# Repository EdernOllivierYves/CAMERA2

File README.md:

# CAMERA2
It is an upgrade with the DR specification of the optical sensor I have received 10th of june 2025.

I have designed the camera around the piece of metal "cache4", with the software autodesk FUSION, in order to complete my project.

Then it should be manufactured with the mechanical drawing, and the pieces of metal can be made at the website "www.usineur.fr".

BR, EO.

PS :  To solder the components you also need to buy capacitors and resistors, for example on the "www.mchobby.be" website.

Here again, I do join the list of the electronical components for soldering on the printed circuit board :

9 Capacitors of 10nF 50V

9 Capacitors of 100nF 50V

9 Capacitors of 10µF AVX 16V

7 Capacitors of 1µF AVX 25V

2 Capacitors electrolytic of 10µF 25V

19 x 36 Pin Header Female (for the socket of the optical sensor)

1 x 40 Pin Header Male (for the arduino connector of the FPGA board)

2 x 25 Pin Header Male (for the parallel port of the circuit board)

7 Potentiometers of 1KOhms 3296W

1 Sensor MT9M413STMDR

1 DEL 3mm

1 Resistor 430Ohms

1 Resistor 2K2Ohms

1 Resistor 10KOhms

1 Transistor BC550B TO92 45V

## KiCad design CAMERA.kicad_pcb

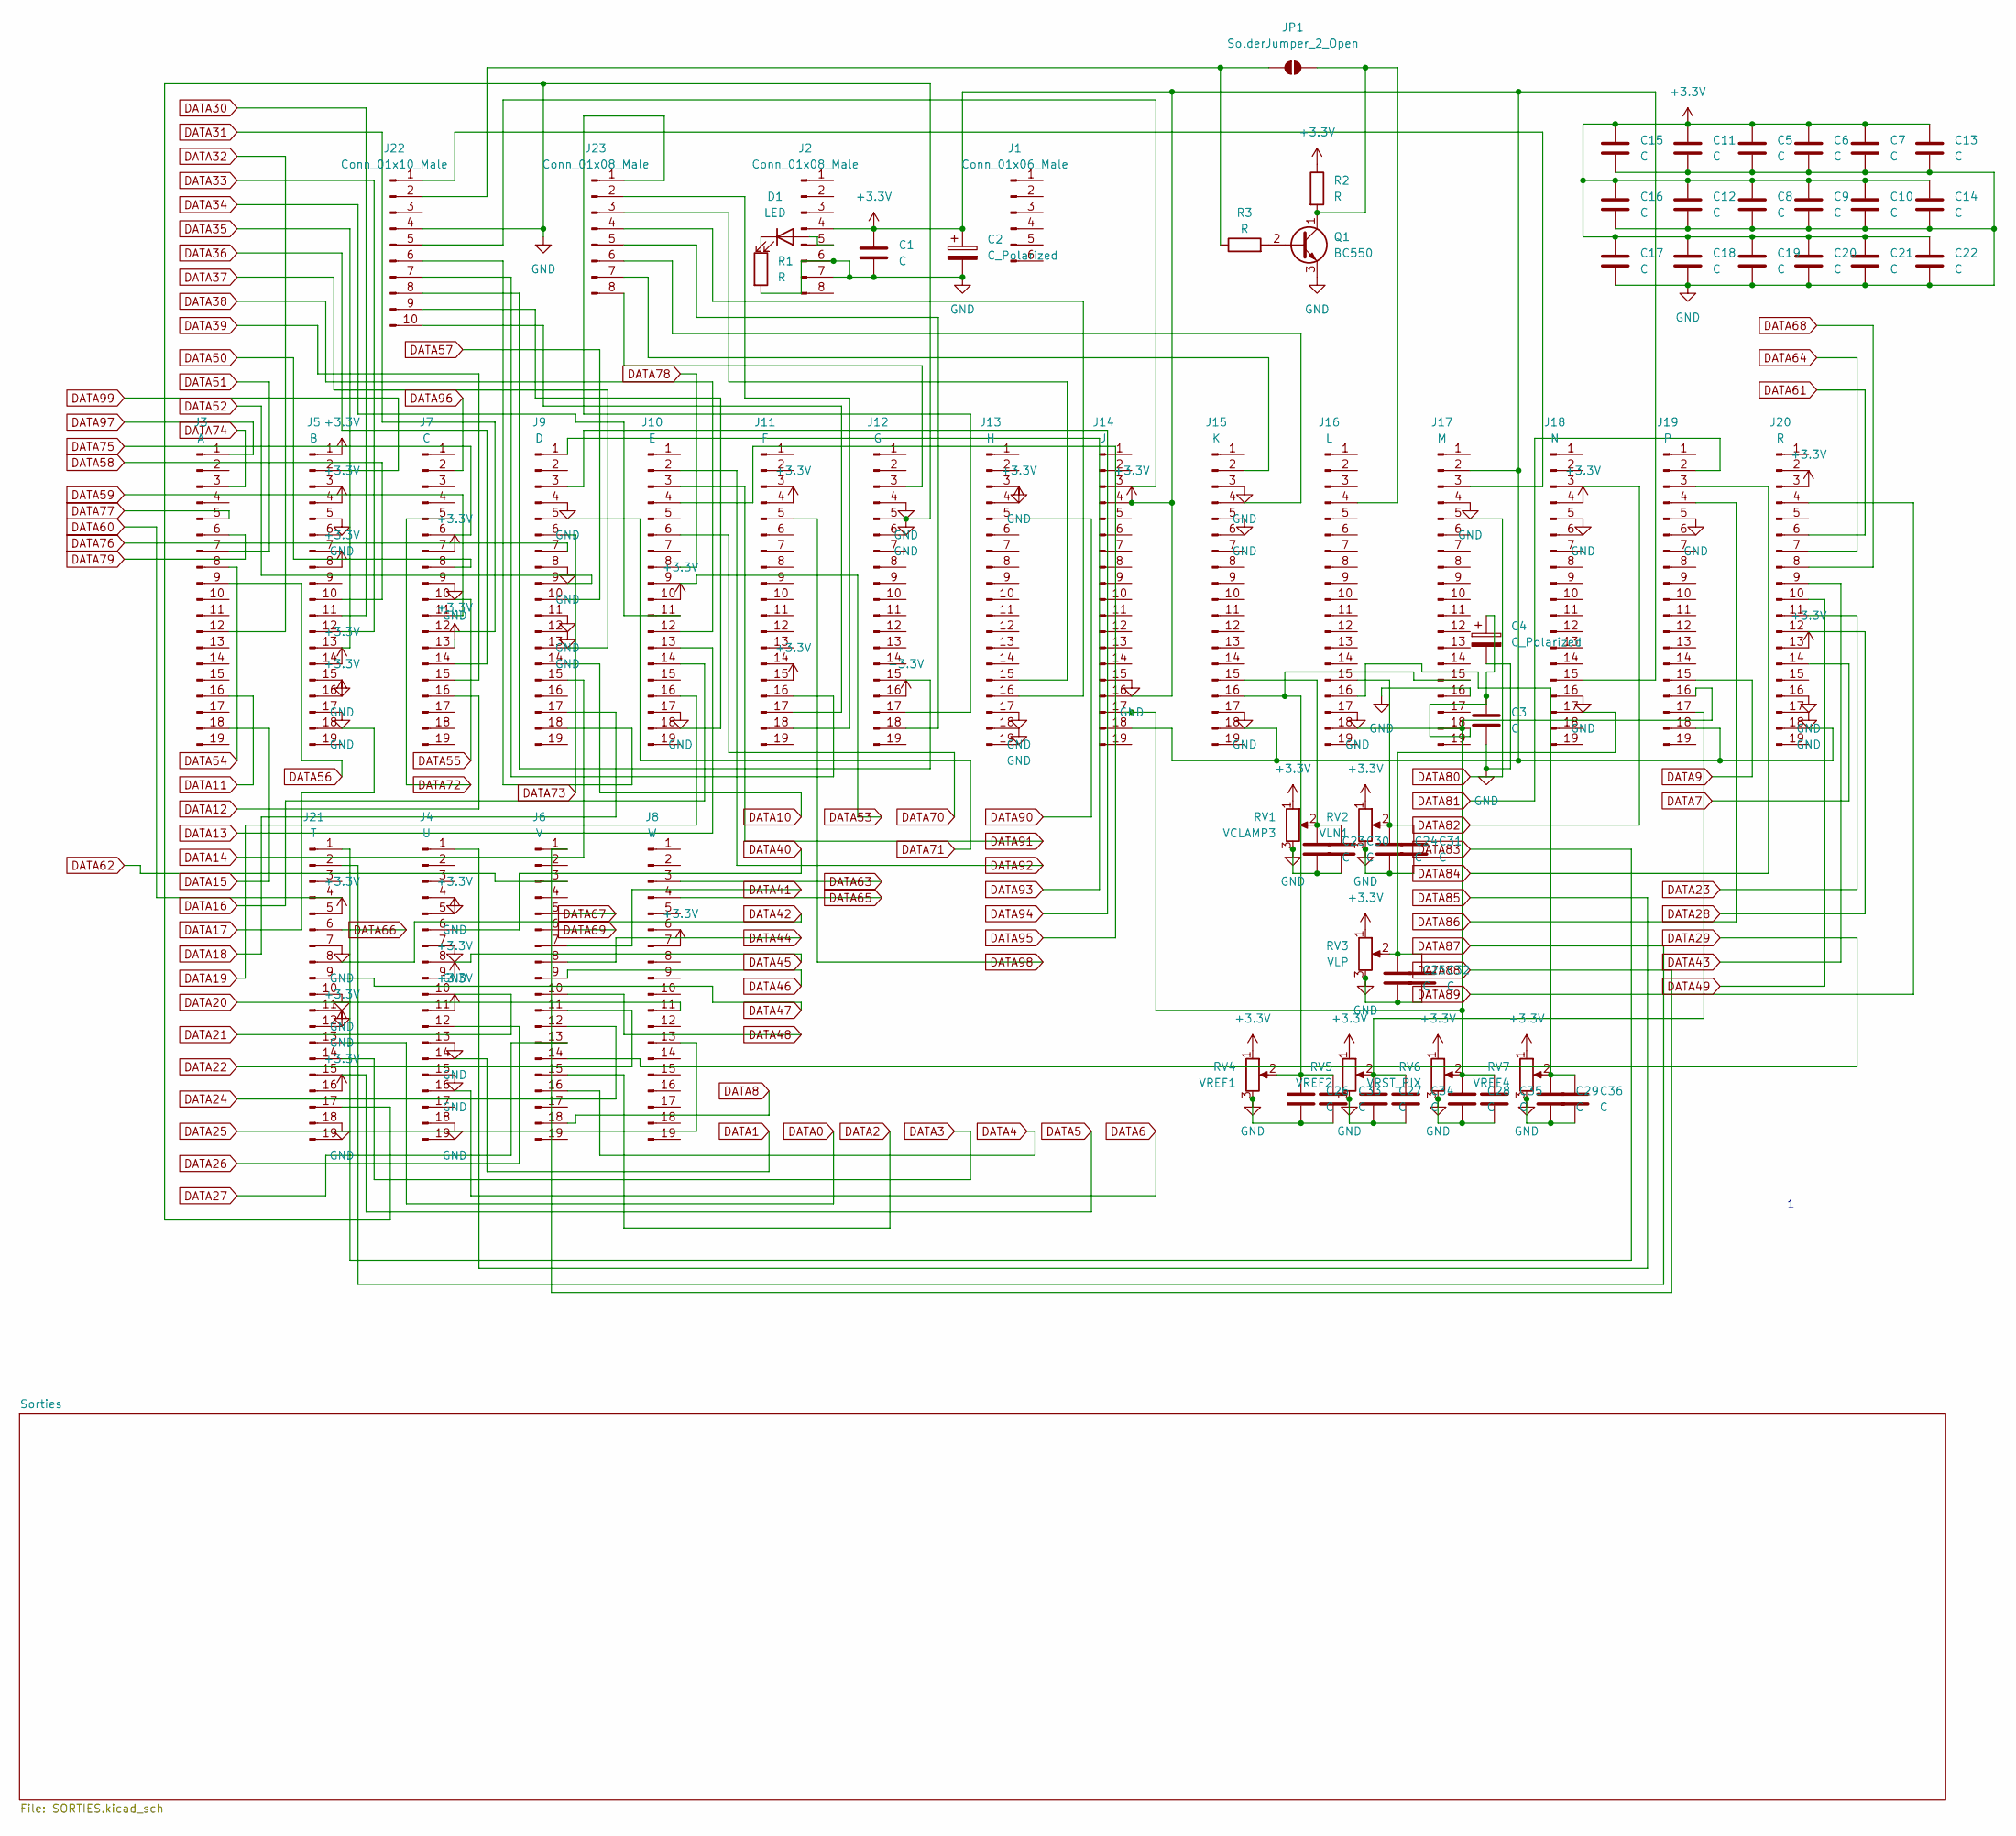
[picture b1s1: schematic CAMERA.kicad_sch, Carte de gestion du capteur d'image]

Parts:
C1, C3, C30, C31, C32, C33, C34, C35, C36: C; C_Radial_D5.0mm_H5.0mm_P2.00mm
C2, C4: C_Polarized; CP_Radial_Tantal_D5.0mm_P2.50mm
C5, C6, C7, C8, C9, C10, C11, C12, C13, C14, C15, C16, C17, C18, C19, C20, C21, C22, C23, C24, C25, C26, C27, C28, C29: C; C_Rect_L4.0mm_W2.5mm_P2.50mm
D1: LED; LED_D3.0mm
J1: Conn_01x06_Male; PinHeader_1x06_P2.54mm_Horizontal
J2, J23: Conn_01x08_Male; PinHeader_1x08_P2.54mm_Horizontal
J3: A; PinHeader_1x19_P2.54mm_Vertical
J4: U; PinHeader_1x19_P2.54mm_Vertical
J5: B; PinHeader_1x19_P2.54mm_Vertical
J6: V; PinHeader_1x19_P2.54mm_Vertical
J7: C; PinHeader_1x19_P2.54mm_Vertical
J8: W; PinHeader_1x19_P2.54mm_Vertical
J9: D; PinHeader_1x19_P2.54mm_Vertical
J10: E; PinHeader_1x19_P2.54mm_Vertical
J11: F; PinHeader_1x19_P2.54mm_Vertical
J12: G; PinHeader_1x19_P2.54mm_Vertical
J13: H; PinHeader_1x19_P2.54mm_Vertical
J14: J; PinHeader_1x19_P2.54mm_Vertical
J15: K; PinHeader_1x19_P2.54mm_Vertical
J16: L; PinHeader_1x19_P2.54mm_Vertical
J17: M; PinHeader_1x19_P2.54mm_Vertical
J18: N; PinHeader_1x19_P2.54mm_Vertical
J19: P; PinHeader_1x19_P2.54mm_Vertical
J20: R; PinHeader_1x19_P2.54mm_Vertical
J21: T; PinHeader_1x19_P2.54mm_Vertical
J22: Conn_01x10_Male; PinHeader_1x10_P2.54mm_Horizontal
JP1: SolderJumper_2_Open; SolderJumper-2_P1.3mm_Open_RoundedPad1.0x1.5mm
Q1: BC550; TO-92_Inline
R1, R2, R3: R; R_Axial_DIN0207_L6.3mm_D2.5mm_P10.16mm_Horizontal
RV1: VCLAMP3; Potentiometer_Bourns_3296W_Vertical
RV2: VLN1; Potentiometer_Bourns_3296W_Vertical
RV3: VLP; Potentiometer_Bourns_3296W_Vertical
RV4: VREF1; Potentiometer_Bourns_3296W_Vertical
RV5: VREF2; Potentiometer_Bourns_3296W_Vertical
RV6: VRST_PIX; Potentiometer_Bourns_3296W_Vertical
RV7: VREF4; Potentiometer_Bourns_3296W_Vertical

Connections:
+3.3V: C1.1, C2.1, C5.1, C6.1, C7.1, C8.1, C9.1, C10.1, C11.1, C12.1, C13.1, C14.1, C15.1, C16.1, C17.1, C18.1, C19.1, C20.1, C21.1, C22.1, J2.4, J4.5, J4.9, J4.11, J5.1, J5.4, J5.8, J5.14, J5.16, J7.7, J7.13, J8.7, J10.10, J11.4, J11.15, J12.16, J13.4, J14.4, J14.16, J14.18, J15.18, J17.2, J18.4, J18.15, J19.18, J20.3, J20.13, J20.18, J21.5, J21.12, J21.16, R2.1, RV1.1, RV2.1, RV3.1, RV4.1, RV5.1, RV6.1, RV7.1
DATA0: J21.13; also elsewhere on the board
DATA1: J4.14; also elsewhere on the board
DATA2: J6.15; also elsewhere on the board
DATA3: J21.14; also elsewhere on the board
DATA4: J6.16; also elsewhere on the board
DATA5: J21.15; also elsewhere on the board
DATA6: J4.16; also elsewhere on the board
DATA7: J20.14; also elsewhere on the board
DATA8: J6.18; also elsewhere on the board
DATA9: J19.15; also elsewhere on the board
DATA10: J9.14; also elsewhere on the board
DATA11: J3.16; also elsewhere on the board
DATA12: J7.16; also elsewhere on the board
DATA13: J10.13; also elsewhere on the board
DATA14: J9.15; also elsewhere on the board
DATA15: J3.18; also elsewhere on the board
DATA16: J10.14; also elsewhere on the board
DATA17: J5.18; also elsewhere on the board
DATA18: J9.17; also elsewhere on the board
DATA19: J10.16; also elsewhere on the board
DATA20: J8.11; also elsewhere on the board
DATA21: J4.10; also elsewhere on the board
DATA22: J6.11; also elsewhere on the board
DATA23: J20.11; also elsewhere on the board
DATA24: J6.12; also elsewhere on the board
DATA25: J8.13; also elsewhere on the board
DATA26: J4.12; also elsewhere on the board
DATA27: J6.13; also elsewhere on the board
DATA28: J20.12; also elsewhere on the board
DATA29: J6.14; also elsewhere on the board
DATA30: J5.11; also elsewhere on the board
DATA31: J7.12; also elsewhere on the board
DATA32: J3.12; also elsewhere on the board
DATA33: J5.12; also elsewhere on the board
DATA34: J10.11; also elsewhere on the board
DATA35: J5.13; also elsewhere on the board
DATA36: J7.14; also elsewhere on the board
DATA37: J9.13; also elsewhere on the board
DATA38: J10.12; also elsewhere on the board
DATA39: J7.15; also elsewhere on the board
DATA40: J4.6; also elsewhere on the board
DATA41: J6.7; also elsewhere on the board
DATA42: J21.8; also elsewhere on the board
DATA43: J20.9; also elsewhere on the board
DATA44: J6.8; also elsewhere on the board
DATA45: J4.8; also elsewhere on the board
DATA46: J6.9; also elsewhere on the board
DATA47: J21.9; also elsewhere on the board
DATA48: J6.10; also elsewhere on the board
DATA49: J20.10; also elsewhere on the board
DATA50: J7.8; also elsewhere on the board
DATA51: J3.7; also elsewhere on the board
DATA52: J9.9; also elsewhere on the board
DATA53: J10.9; also elsewhere on the board
DATA54: J3.8; also elsewhere on the board
DATA55: J7.10; also elsewhere on the board
DATA56: J3.9; also elsewhere on the board
DATA57: J9.10; also elsewhere on the board
DATA58: J5.10; also elsewhere on the board
DATA59: J7.11; also elsewhere on the board
DATA60: J21.4; also elsewhere on the board
DATA61: J20.6; also elsewhere on the board
DATA62: J6.3; also elsewhere on the board
DATA63: J8.3; also elsewhere on the board
DATA64: J20.7; also elsewhere on the board
DATA65: J8.4; also elsewhere on the board
DATA66: J21.6; also elsewhere on the board
DATA67: J6.5; also elsewhere on the board
DATA68: J20.8; also elsewhere on the board
DATA69: J6.6; also elsewhere on the board
DATA70: J10.6; also elsewhere on the board
DATA71: J9.5; also elsewhere on the board
DATA72: J7.5; also elsewhere on the board
DATA73: J9.6; also elsewhere on the board
DATA74: J3.3; also elsewhere on the board
DATA75: J7.6; also elsewhere on the board
DATA76: J9.7; also elsewhere on the board
DATA77: J3.5; also elsewhere on the board
DATA78: J10.8; also elsewhere on the board
DATA79: J3.6; also elsewhere on the board
DATA80: J17.5; also elsewhere on the board
DATA81: J19.2; also elsewhere on the board
DATA82: J18.3; also elsewhere on the board
DATA83: J21.1; also elsewhere on the board
DATA84: J19.3; also elsewhere on the board
DATA85: J4.1; also elsewhere on the board
DATA86: J19.4; also elsewhere on the board
DATA87: J21.2; also elsewhere on the board
DATA88: J6.1; also elsewhere on the board
DATA89: J20.4; also elsewhere on the board
DATA90: J13.5; also elsewhere on the board
DATA91: J10.3; also elsewhere on the board
DATA92: J10.2; also elsewhere on the board
DATA93: J9.1; also elsewhere on the board
DATA94: J9.3; also elsewhere on the board
DATA95: J10.4; also elsewhere on the board
DATA96: J7.2; also elsewhere on the board
DATA97: J3.1; also elsewhere on the board
DATA98: J11.5; also elsewhere on the board
DATA99: J5.2; also elsewhere on the board
GND: C1.2, C2.2, C3.2, C4.2, C5.2, C6.2, C7.2, C8.2, C9.2, C10.2, C11.2, C12.2, C13.2, C14.2, C15.2, C16.2, C17.2, C18.2, C19.2, C20.2, C21.2, C22.2, C23.2, C24.2, C25.2, C26.2, C27.2, C28.2, C29.2, C30.2, C31.2, C32.2, C33.2, C34.2, C35.2, C36.2, J2.6, J2.7, J4.4, J4.7, J4.13, J4.15, J4.18, J5.5, J5.15, J5.17, J7.9, J9.4, J9.8, J9.11, J9.12, J10.17, J12.4, J12.5, J13.3, J13.17, J13.18, J14.15, J15.3, J15.5, J15.17, J16.17, J17.4, J17.16, J18.5, J18.16, J19.5, J20.16, J20.17, J21.7, J21.10, J21.11, J21.17, J21.18, J22.4, Q1.3 (E), R1.2, RV1.3, RV2.3, RV3.3, RV4.3, RV5.3, RV6.3, RV7.3
unnamed: D1.2 (A), J2.5
unnamed: D1.1 (K), R1.1
unnamed: J10.18, J22.9
unnamed: J11.16, J22.7
unnamed: J11.17, J22.10
unnamed: J11.18, J23.2
unnamed: J12.3, J23.8
unnamed: J12.15, J22.8
unnamed: J12.17, J23.1
unnamed: J12.18, J23.5
unnamed: J13.15, J23.3
unnamed: J13.16, J23.4
unnamed: J14.3, J22.5
unnamed: C28.1, C35.1, J14.17, J16.18, J19.16, RV6.2
unnamed: J15.2, J23.7
unnamed: J15.4, J23.6
unnamed: C23.1, C30.1, J15.15, RV1.2
unnamed: C26.1, C33.1, J15.16, J17.15, RV4.2
unnamed: J16.4, JP1.1 (A), Q1.1 (C), R2.2
unnamed: C24.1, C31.1, J16.15, RV2.2
unnamed: C29.1, C36.1, J16.16, RV7.2
unnamed: J17.3, J22.1
unnamed: C3.1, C4.1, J17.18
unnamed: C25.1, C32.1, J18.17, RV3.2
unnamed: C27.1, C34.1, J19.17, RV5.2
unnamed: J22.2, JP1.2 (B), R3.1
unnamed: J9.18, J22.6
unnamed: Q1.2 (B), R3.2

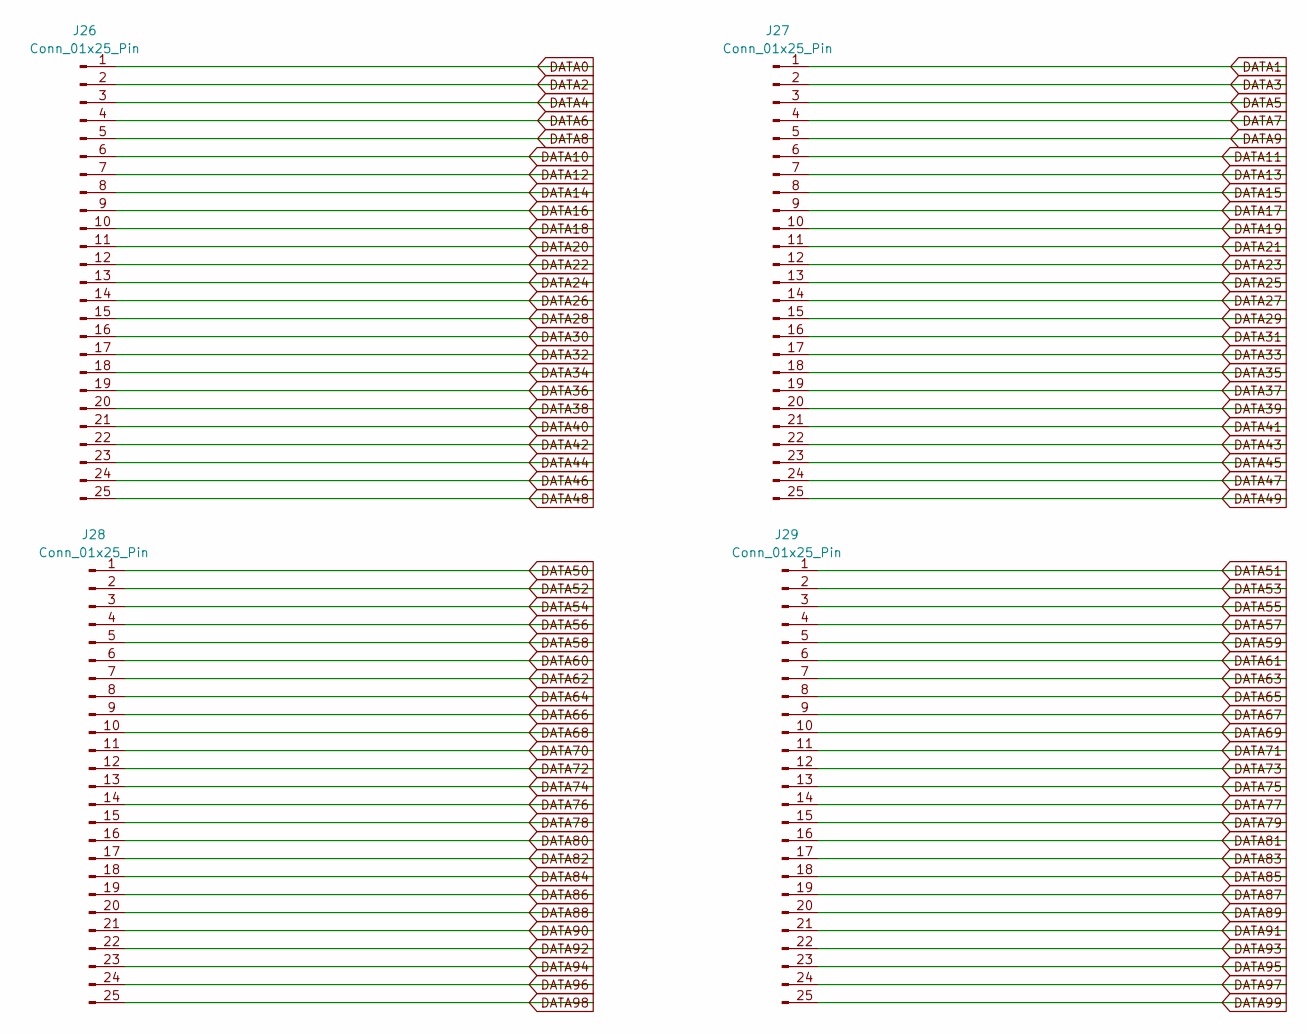
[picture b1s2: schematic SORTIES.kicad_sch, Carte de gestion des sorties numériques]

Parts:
J26, J27, J28, J29: Conn_01x25_Pin; Molex_SL_171971-0025_1x25_P2.54mm_Vertical

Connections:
DATA0: J26.1; also elsewhere on the board
DATA1: J27.1; also elsewhere on the board
DATA2: J26.2; also elsewhere on the board
DATA3: J27.2; also elsewhere on the board
DATA4: J26.3; also elsewhere on the board
DATA5: J27.3; also elsewhere on the board
DATA6: J26.4; also elsewhere on the board
DATA7: J27.4; also elsewhere on the board
DATA8: J26.5; also elsewhere on the board
DATA9: J27.5; also elsewhere on the board
DATA10: J26.6; also elsewhere on the board
DATA11: J27.6; also elsewhere on the board
DATA12: J26.7; also elsewhere on the board
DATA13: J27.7; also elsewhere on the board
DATA14: J26.8; also elsewhere on the board
DATA15: J27.8; also elsewhere on the board
DATA16: J26.9; also elsewhere on the board
DATA17: J27.9; also elsewhere on the board
DATA18: J26.10; also elsewhere on the board
DATA19: J27.10; also elsewhere on the board
DATA20: J26.11; also elsewhere on the board
DATA21: J27.11; also elsewhere on the board
DATA22: J26.12; also elsewhere on the board
DATA23: J27.12; also elsewhere on the board
DATA24: J26.13; also elsewhere on the board
DATA25: J27.13; also elsewhere on the board
DATA26: J26.14; also elsewhere on the board
DATA27: J27.14; also elsewhere on the board
DATA28: J26.15; also elsewhere on the board
DATA29: J27.15; also elsewhere on the board
DATA30: J26.16; also elsewhere on the board
DATA31: J27.16; also elsewhere on the board
DATA32: J26.17; also elsewhere on the board
DATA33: J27.17; also elsewhere on the board
DATA34: J26.18; also elsewhere on the board
DATA35: J27.18; also elsewhere on the board
DATA36: J26.19; also elsewhere on the board
DATA37: J27.19; also elsewhere on the board
DATA38: J26.20; also elsewhere on the board
DATA39: J27.20; also elsewhere on the board
DATA40: J26.21; also elsewhere on the board
DATA41: J27.21; also elsewhere on the board
DATA42: J26.22; also elsewhere on the board
DATA43: J27.22; also elsewhere on the board
DATA44: J26.23; also elsewhere on the board
DATA45: J27.23; also elsewhere on the board
DATA46: J26.24; also elsewhere on the board
DATA47: J27.24; also elsewhere on the board
DATA48: J26.25; also elsewhere on the board
DATA49: J27.25; also elsewhere on the board
DATA50: J28.1; also elsewhere on the board
DATA51: J29.1; also elsewhere on the board
DATA52: J28.2; also elsewhere on the board
DATA53: J29.2; also elsewhere on the board
DATA54: J28.3; also elsewhere on the board
DATA55: J29.3; also elsewhere on the board
DATA56: J28.4; also elsewhere on the board
DATA57: J29.4; also elsewhere on the board
DATA58: J28.5; also elsewhere on the board
DATA59: J29.5; also elsewhere on the board
DATA60: J28.6; also elsewhere on the board
DATA61: J29.6; also elsewhere on the board
DATA62: J28.7; also elsewhere on the board
DATA63: J29.7; also elsewhere on the board
DATA64: J28.8; also elsewhere on the board
DATA65: J29.8; also elsewhere on the board
DATA66: J28.9; also elsewhere on the board
DATA67: J29.9; also elsewhere on the board
DATA68: J28.10; also elsewhere on the board
DATA69: J29.10; also elsewhere on the board
DATA70: J28.11; also elsewhere on the board
DATA71: J29.11; also elsewhere on the board
DATA72: J28.12; also elsewhere on the board
DATA73: J29.12; also elsewhere on the board
DATA74: J28.13; also elsewhere on the board
DATA75: J29.13; also elsewhere on the board
DATA76: J28.14; also elsewhere on the board
DATA77: J29.14; also elsewhere on the board
DATA78: J28.15; also elsewhere on the board
DATA79: J29.15; also elsewhere on the board
DATA80: J28.16; also elsewhere on the board
DATA81: J29.16; also elsewhere on the board
DATA82: J28.17; also elsewhere on the board
DATA83: J29.17; also elsewhere on the board
DATA84: J28.18; also elsewhere on the board
DATA85: J29.18; also elsewhere on the board
DATA86: J28.19; also elsewhere on the board
DATA87: J29.19; also elsewhere on the board
DATA88: J28.20; also elsewhere on the board
DATA89: J29.20; also elsewhere on the board
DATA90: J28.21; also elsewhere on the board
DATA91: J29.21; also elsewhere on the board
DATA92: J28.22; also elsewhere on the board
DATA93: J29.22; also elsewhere on the board
DATA94: J28.23; also elsewhere on the board
DATA95: J29.23; also elsewhere on the board
DATA96: J28.24; also elsewhere on the board
DATA97: J29.24; also elsewhere on the board
DATA98: J28.25; also elsewhere on the board
DATA99: J29.25; also elsewhere on the board

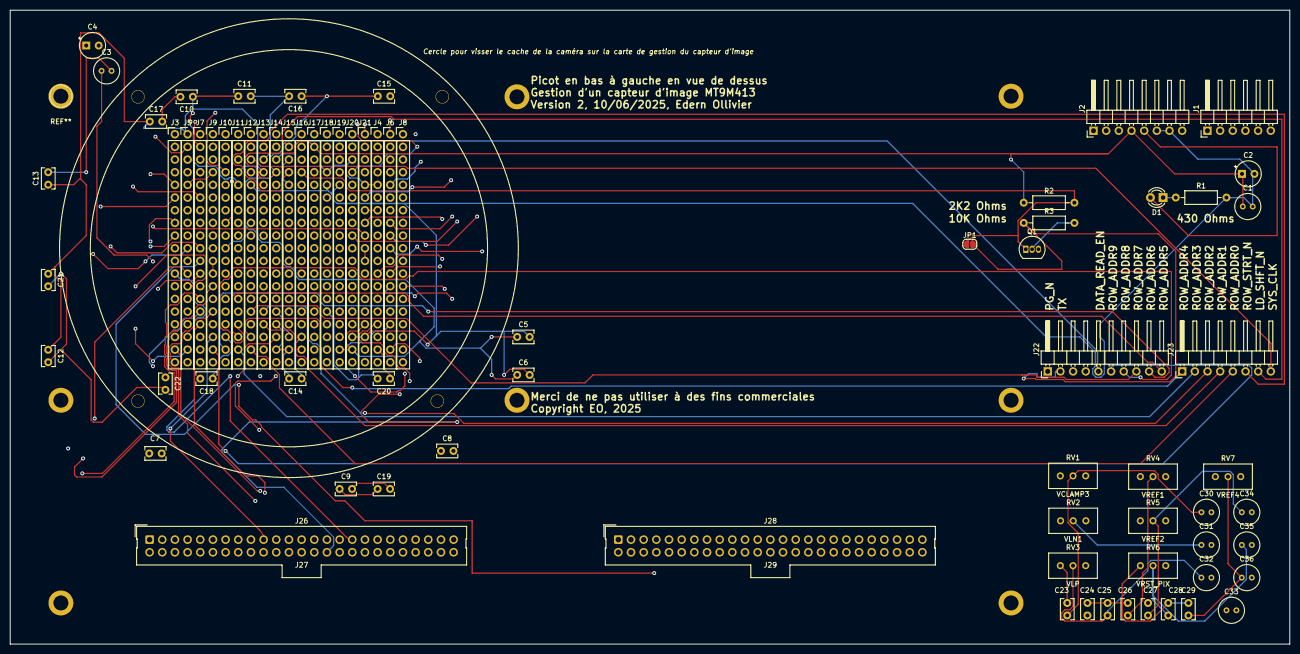
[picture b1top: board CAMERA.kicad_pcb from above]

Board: 6 copper layers, 256.5 x 127.1 mm, 76 parts (0 on the bottom side), 130 nets.

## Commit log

2025-07-02 Add files via upload
    Avec la bride

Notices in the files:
CAMERA.kicad_pcb:
Copyright EO, 2025
